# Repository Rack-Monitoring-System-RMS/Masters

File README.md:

# Masters

For "Rack Manager 🧠" [check out this](https://github.com/Rack-Monitoring-System-RMS/Masters/blob/main/Rack-Manager/README.md) <br>
For "Debug Dongle 🐴" [check out this](https://github.com/Rack-Monitoring-System-RMS/Masters/blob/main/Debug-Dongle/README.md)

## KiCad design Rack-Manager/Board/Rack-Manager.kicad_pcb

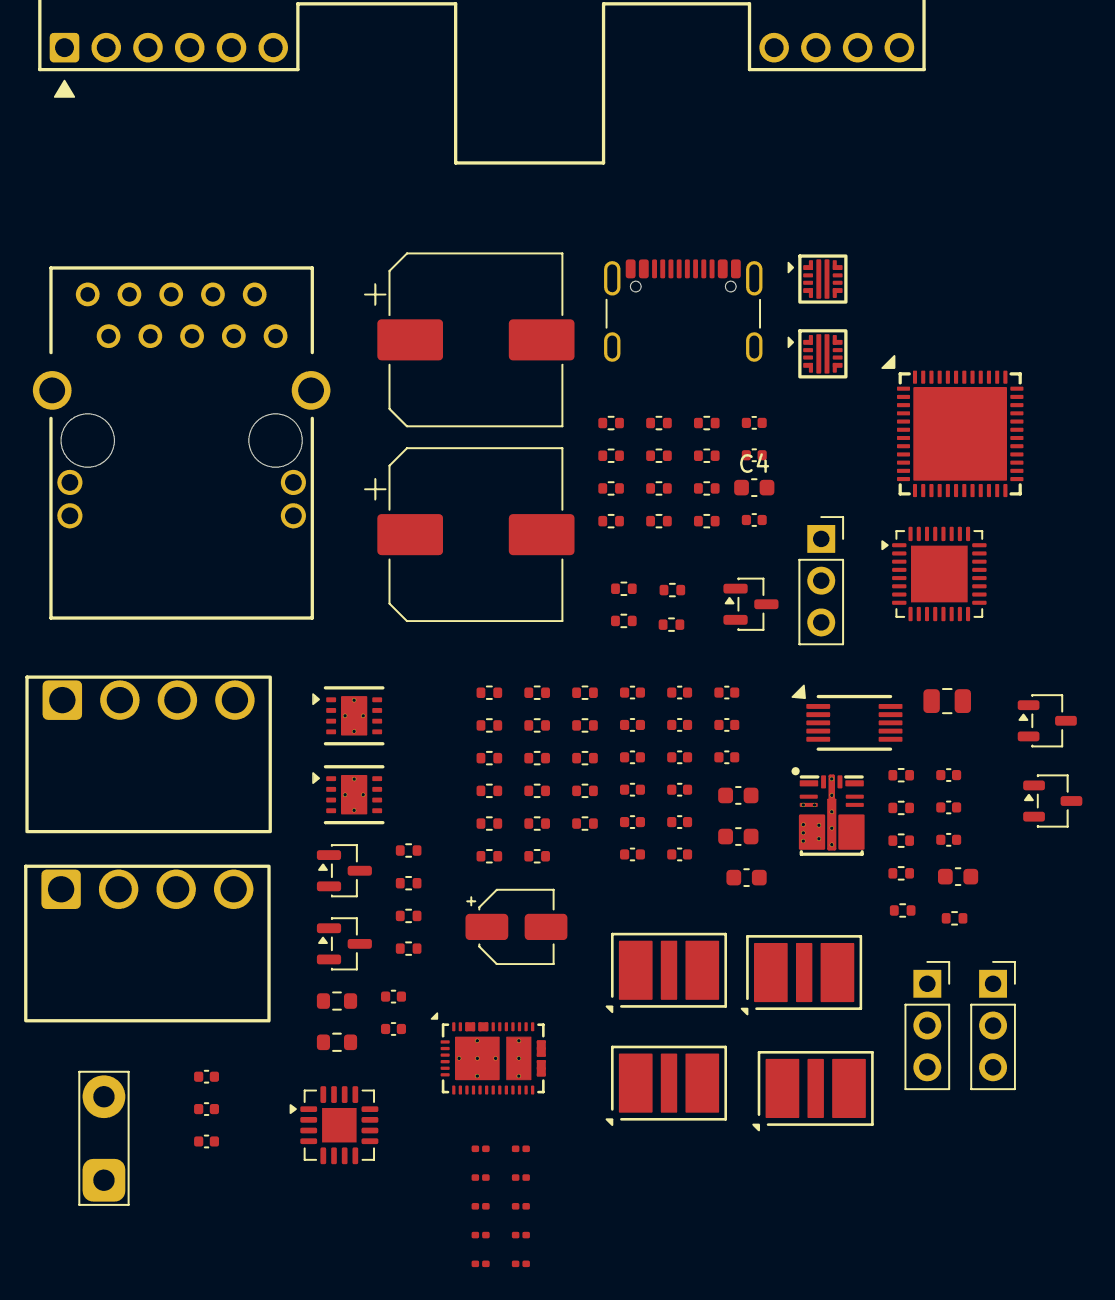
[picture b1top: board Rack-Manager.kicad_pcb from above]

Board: 2 copper layers, 118 parts (0 on the bottom side), 90 nets, no tracks yet.

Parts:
C1, C2: 120nF; C_0402_1005Metric
C3, C4#2, C5, C6: C_0603_1608Metric
C4: C_0402_1005Metric
C7, C8: 220uF; CP_Elec_10x10
C9: 4.7uF; C_0805_2012Metric
C10: 1uF; C_0603_1608Metric
C11, C12, C13: 1uF; C_0402_1005Metric
C14, C15, C16, C17, C19, C20, C21, C22, C23, C24, C25, C26, C27, C30, C31, C32, C33, C34: 100nF; C_0402_1005Metric
C18: 3.3uF; CP_Elec_4x5.7
C28, C29: 8pF; C_0402_1005Metric
D1, D2, D2#2: SM712; SOT-23
F1, F2, F3, F4: TBU-CA065-300-WH; TBU-CA
J1: ARJM11C7-114-BA-EW2; ARJM11 - Package C
J2: USB4105-GT-A; USB_C_Receptacle_GCT_USB4105-xx-A_16P_TopMnt_Horizontal
J3, J4: TBP03R1-350-04BE
J5, J5#2, J6: Conn_01x03_Pin; PinSocket_1x03_P2.54mm_Vertical
JP1: Jumper_3_Bridged12; TestPoint_2Pads_Pitch5.08mm_Drill1.3mm
Q1, Q3: NTR4003NT1G; SOT-23-3
R1: 698R; R_0402_1005Metric
R2, R5, R12: 100k; R_0402_1005Metric
R3: 33k; R_0402_1005Metric
R4, R7, R8, R9, R18, R19, R20, R21, R39, R40, R41, R42, R59: 10k; R_0402_1005Metric
R6: 13k; R_0402_1005Metric
R10, R14: 3.6k; R_0402_1005Metric
R11: 820R; R_0402_1005Metric
R13: 1.5k; R_0402_1005Metric
R15: 20k; R_0402_1005Metric
R16, R17: 330R; R_0402_1005Metric
R22: 12k; R_0402_1005Metric
R23: 300; R_0402_1005Metric
R24, R25, R26, R27: 3.3; R_0402_1005Metric
R28: 1M; R_0402_1005Metric
R29, R30, R31, R32: 49.9; R_0402_1005Metric
R33, R36: 120; R_0603_1608Metric
R33#2: 120; R_0402_1005Metric
R34, R35, R37, R38: 10; R_0402_1005Metric
R43, R44, R45, R46, R48, R55, R56, R57, R58, R60: 10k; R_0201_0603Metric
RV1: 10k; R_0402_1005Metric
U1: Ag9712-FL; Ag9700
U2, U3: TPS259470A; RPW0010A
U4: TLVM23625; RDN0011A
U5: INA220; DGS0010A
U6: STM32G0B1KCU7; QFN-32-1EP_5x5mm_P0.5mm_EP3.45x3.45mm
U7: W6100Q; QFN-48 (Thermal Pad)
U8, U9: THVD1450DRBR; DRB0008F
U10: INA3221; Texas_RGV0016A_VQFN-16-1EP_4x4mm_P0.65mm_EP2.1x2.1mm
U11: TPS25730D; REF0038A

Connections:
3V3: C12.1, C13.1, C30.1, C31.1, C32.1, R7.1, R8.1, R9.1, R14.1, R39.2, R40.2, R41.2, R42.2, R48.2, R55.2, R56.2, R60.2, U4.4 (V_{OUT}), U8.8 (Vcc), U9.8 (Vcc), U10.4 (VS), U10.16 (VPU)
/Bus output/V_{IN+1}: C33.1, U10.12 (IN+1)
/Bus output/V_{IN+2}: C34.1, U10.15 (IN+2)
/Bus output/V_{IN+3}: R57.2, R59.1, U10.2 (IN+3)
/Bus output/V_{IN-1}: C33.2, U10.11 (IN-1)
/Bus output/V_{IN-2}: C34.2, U10.14 (IN-2)
/Bus output/V_{IN-3}: R58.2, R59.2, U10.1 (IN-3)
/Ethernet/ETH_1V2A: C23.1, U7.4 (1V2A)
/Ethernet/ETH_1V2D: C19.1, C20.1, C21.1, C22.1, U7.13 (1V2D_{[1]}), U7.22 (1V2D_{[2]}), U7.31 (1V2D_{[3]}), U7.45 (1V2D_{[4]})
/Ethernet/ETH_1V2O: C18.1, U7.14 (1V2O)
/Ethernet/ETH_3V3A: C14.1, C15.1, C26.1, C27.1, J1.4 (R_{CT}), J1.9 (T_{CT}), U7.8 (3V3A_{[1]}), U7.15 (3V3A_{[2]})
/Ethernet/ETH_3V3D: C16.1, C17.1, J1.11 (A_{GRN}), J1.13 (A_{YEL}), U7.24 (3V3D_{[1]}), U7.36 (3V3D_{[2]})
/Ethernet/LED_GREEN: R16.2, U7.17 (~LINKn)
/Ethernet/LED_YELLOW: R17.2, U7.20 (~ACTIVEn)
/Ethernet/RX+: J1.5 (R_{D+}), R26.2, R29.1
/Ethernet/RX-: J1.3 (R_{D-}), R24.2, R30.1
/Ethernet/TX+: J1.10 (T_{D+}), R25.1, R31.1
/Ethernet/TX-: J1.8 (T_{D-}), R27.1, R32.1
A1: F1.3, J3.3
A2: F3.3, J4.3
AGND: C1.2, C2.2, C3.2, C4.2, C4#2.2, C5.2, C6.2, C7.2, C8.2, C9.2, C10.2, C11.2, C12.2, C13.2, C14.2, C15.2, C16.2, C17.2, C18.2, C19.2, C20.2, C21.2, C22.2, C23.2, C24.2, C25.2, C26.2, C27.2, C28.2, C29.2, C30.2, C31.2, C32.2, D1.3 (common), D2.3 (common), D2#2.3 (common), J2.A1 (GND), J2.A12 (GND), J2.B1 (GND), J2.B12 (GND), J3.2, J4.2, JP1.1 (A), Q1.2 (S), Q3.2 (S), R4.2, R6.1, R10.2, R11.2, R13.2, R15.2, R18.2, R19.2, R20.2, R21.2, R23.2, R44.1, R46.1, R57.1, R58.1, RV1.1, U1.7 (V_{DC}-), U2.8 (GND), U3.8 (GND), U4.10 (GND), U7.1 (GNDA_{[1]}), U7.7 (GNDA_{[2]}), U7.10 (GND_{[1]}), U7.16 (GNDA_{[3]}), U7.46 (GND_{[2]}), U7.49 (THERMAL_PAD), U8.5 (GND), U9.5 (GND), U10.3 (GND), U10.17 (EP)
B1: F2.3, J3.4
B2: F4.3, J4.4
BUS1_{DE/~RE}: R40.1, U8.2 (~RE), U8.3 (DE)
BUS1_{RX}: R39.1, U8.1 (R)
BUS2_{DE/~RE}: R41.1, U9.2 (~RE), U9.3 (DE)
BUS2_{RX}: R42.1, U9.1 (R)
D+: J2.A7 (D-), J2.B7 (D-)
D-: J2.A6 (D+), J2.B6 (D+)
EN_BUS_1: Q1.1 (G), Q3.1 (G), R44.2, R46.2
Earth: J1.15 (MH_{[1]}), J1.16 (MH_{[2]}), J2.S1 (SHIELD)
unnamed: C24.1, R29.2, R30.2
unnamed: C25.1, R31.2, R32.2
unnamed: D1.1 (A1), F1.1, R34.2
unnamed: D1.2 (A2), F2.1, R35.2
unnamed: D2.1 (A1), D2#2.1 (A1), F3.1, R37.2
unnamed: D2.2 (A2), D2#2.2 (A2), F4.1, R38.2
unnamed: J1.7 (VC_{[1]}+), U1.1 (V_{A1})
unnamed: J1.2 (VC_{[1]}-), U1.2 (V_{A1})
unnamed: J1.6 (VC_{[2]}+), U1.3 (V_{B1})
unnamed: J1.1 (VC_{[2]}-), U1.4 (V_{B2})
unnamed: J1.12 (K_{GRN}), R16.1
unnamed: J1.14 (K_{YEL}), R17.1
unnamed: J5.1, J5.2, J5#2.1, J5#2.2, R34.1, U8.6 (A)
unnamed: J5.3, J5#2.3, R33#2.2
unnamed: J6.1, J6.2, R37.1, U9.6 (A)
unnamed: J6.3, R36.1
unnamed: JP1.2 (C), U10.5 (A0)
unnamed: Q1.3 (D), R43.1
unnamed: Q3.3 (D), R45.1
unnamed: R22.2, R23.1
unnamed: RV1.2, U1.9 (ADJ)
unnamed: R1.1, U1.5 (CP_{[1]})
unnamed: R1.2, U1.6 (CP_{[2]})
unnamed: R5.1, U1.8 (V_{DC}+), U2.5 (IN)
unnamed: R5.2, R6.2, U2.1 (ENABLE)
unnamed: R10.1, U2.9 (I_{LIM})
unnamed: C1.1, U2.10 (I_{TIMER})
unnamed: C4.1, C5.1, C6.1, U2.7 (dV/dT)
unnamed: R2.2, R3.1, U3.1 (ENABLE)
unnamed: J2.A4 (VBUS), J2.A9 (VBUS), J2.B4 (VBUS), J2.B9 (VBUS), R2.1, U3.5 (IN)
unnamed: R3.2, R4.1, U3.2 (OVLO)
unnamed: R11.1, U3.9 (I_{LIM})
unnamed: C2.1, U3.10 (I_{TIMER})
unnamed: C3.1, C4#2.1, U3.7 (dV/dT)
unnamed: R12.2, U4.2 (EN)
unnamed: R13.1, R14.2, U4.9 (FB)
unnamed: R15.1, U4.11 (RT)
unnamed: C11.1, U4.8 (V_{CC})
unnamed: R18.1, U7.25 (MODE_{[0]})
unnamed: R19.1, U7.26 (MODE_{[1]})
unnamed: R20.1, U7.27 (MODE_{[2]})
unnamed: R21.1, U7.28 (MODE_{[3]})
unnamed: R22.1, U7.9 (RSET_BG)
unnamed: C29.1, R28.2, U7.12 (XSCI)
unnamed: C28.1, R28.1, U7.11 (XSCO)
unnamed: R26.1, U7.6 (RXI+)
unnamed: R24.1, U7.5 (RXI-)
unnamed: R25.2, U7.3 (TXO+)
unnamed: R27.2, U7.2 (TXO-)
unnamed: R33.2, R33#2.1, R35.1, U8.7 (B)
unnamed: R36.2, R38.1, U9.7 (B)
unnamed: R55.1, U10.9 (CRITICAL)
unnamed: R48.1, U10.10 (PV)
unnamed: R60.1, U10.13 (TC)
unnamed: R56.1, U10.8 (WARNING)
PoE_Inhibit: R8.2, U2.2 (OVLO), U3.3 (AUXOFF)
VCC_{SYS}: C7.1, C8.1, C9.1, C10.1, R12.1, U2.6 (OUT), U3.6 (OUT), U4.3 (V_{IN})
~PD_FLT: R9.2, U3.4 (~FLT)
~PoE_FLT: R7.2, U2.4 (~FLT)

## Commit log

2025-08-18 Create a
2025-08-18 Added KiCAD empty project in "Board" folder and removed "placeholder file a.md"
2025-08-18 Rename Rack-Manager.md to README.md
2025-08-18 Rename Debug-Dongle.md to README.md
2025-10-20 Added: Abracon, Microchip, STMicroelectronics, Same Sky, Silvertel, Texas Instruments and WIZnet project libraries for KiCAD.
2025-10-20 Updated Texas Instruments library for KiCAD
2025-10-25 Removed unused 3D model on Texas Instruments library for KiCAD.
2025-10-25 Improved some components symbol, also started with schematics design.
2025-10-25 Updated .gitignore
2025-10-25 Removed .bak files from KiCAD libraries.
2025-10-29 Added USB-PD power circuit to the schematics.
2025-10-30 Updated Silvertel and Texas Instruments KiCAD libraries. Continued with the schematics design.
2025-11-05 Updated Texas Instruments and WIZnet KiCAD libraries. Continued with the schematics design.
2025-11-06 Updated Texas Instruments KiCAD library. Continued with the schematics design.
2025-11-24 Fixed README.md just to try
2025-11-25 Continued with the schematic drawing.
2026-01-08 Added Bourns library, updated Texas Instruments library, continued with schematic drawing.
2026-02-06 Added dvdt cap on eFuses and choose PD standalone sink controller
2026-02-06 Added/Updated notes for TODOs
2026-02-09 Added intresting EMC video link
2026-02-13 Updated .gitignore, added USB-C sink controller and fix earth on GDT
2026-02-13 Added the fan management sheet and the mosfets for it
2026-02-15 Completed fan control circuit
2026-02-15 Created dedicated FAN file
2026-02-15 Fixed FAN control link mixed with bus output file
2026-02-15 Added RS485 protection data as task describe and fixed stuff around
2026-02-16 Fixed volteage divider for fan tachometer and fixed other pull-x and divider for the microcontroller
2026-02-16 Found some error or missing stuff and noted on the main sheet
2026-02-17 Added MCU, Fixed USB-C PD Ideal Diode bug and updated the todo notes
2026-06-02 Some fix and kicad update
